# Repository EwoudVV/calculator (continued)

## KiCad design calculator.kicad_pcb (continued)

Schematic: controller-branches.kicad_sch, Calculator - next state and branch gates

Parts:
C1001, C1002, C1003, C1004, C1005, C1006, C1007, C1008, C1009, C1010, C1011, C1012, C1024, C1025, C1027, C1028, C1029, C1030, C1031, C1032, C1033, C1034: 100n; C_0603_1608Metric
U1001, U1004, U1023, U1028: SN74HC04PWR; TSSOP-14_4.4x5mm_P0.65mm
U1002, U1032: SN74HC08PWR; TSSOP-14_4.4x5mm_P0.65mm
U1003, U1007, U1008, U1009, U1010, U1012: SN74HC32PWR; TSSOP-14_4.4x5mm_P0.65mm
U1005, U1006, U1030: SN74HC00PWR; TSSOP-14_4.4x5mm_P0.65mm
U1011: CD74HC27M96; SOIC-14_3.9x8.7mm_P1.27mm
U1017: SN74HC10DR; SOIC-14_3.9x8.7mm_P1.27mm
U1024, U1025, U1033, U1034: CD74HC30M96; SOIC-14_3.9x8.7mm_P1.27mm
U1027, U1029, U1031: SN74HC20DR; SOIC-14_3.9x8.7mm_P1.27mm

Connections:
+5V: C1001.1, C1002.1, C1003.1, C1004.1, C1005.1, C1006.1, C1007.1, C1008.1, C1009.1, C1010.1, C1011.1, C1012.1, C1024.1, C1025.1, C1027.1, C1028.1, C1029.1, C1030.1, C1031.1, C1032.1, C1033.1, C1034.1, U1001.14 (VCC), U1002.14 (VCC), U1003.14 (VCC), U1004.14 (VCC), U1005.14 (VCC), U1006.14 (VCC), U1007.14 (VCC), U1008.14 (VCC), U1009.14 (VCC), U1010.14 (VCC), U1011.14 (VCC), U1012.14 (VCC), U1024.14 (VCC), U1025.12, U1025.14 (VCC), U1027.14 (VCC), U1028.14 (VCC), U1029.14 (VCC), U1030.14 (VCC), U1031.14 (VCC), U1032.2, U1032.14 (VCC), U1033.14 (VCC), U1034.12, U1034.14 (VCC); also elsewhere on the board
/Main controller/Branch decisions/ADVANCE_REQUEST: U1002.9, U1012.3
/Main controller/Branch decisions/ADVANCE_REQUEST_OR_36: U1010.6, U1010.12
/Main controller/Branch decisions/ADVANCE_REQUEST_OR_37: U1010.8, U1010.13
/Main controller/Branch decisions/ADVANCE_REQUEST_OR_38: U1010.11, U1012.1
/Main controller/Branch decisions/ANY_COMMAND: U1010.9, U1031.6
/Main controller/Branch decisions/CONTROLLER_POWER_RESET: U1001.10, U1003.9
/Main controller/Branch decisions/FORCE_CLEAR_OR_9: U1003.8, U1003.12
/Main controller/Branch decisions/INVALID_CODE_OR_7: U1003.3, U1003.4
/Main controller/Branch decisions/INVALID_LOW_CODE: U1003.1, U1029.8
/Main controller/Branch decisions/JUMP_SELECTED: U1002.12, U1030.6
/Main controller/Branch decisions/JUMP_SELECTED_GROUP_0: U1028.11, U1033.8
/Main controller/Branch decisions/JUMP_SELECTED_GROUP_1: U1028.13, U1034.8
/Main controller/Branch decisions/LOAD_BRANCH: U1002.11, U1012.5
/Main controller/Branch decisions/LOAD_REQUEST: U1004.9, U1012.6
/Main controller/Branch decisions/N_CANCEL: U1001.12, U1002.2
/Main controller/Branch decisions/N_CARRY_FLAG: U1001.2, U1007.10, U1008.5
/Main controller/Branch decisions/N_DIV_STAGE_LAST: U1001.8
/Main controller/Branch decisions/N_JUMP_SELECTED_GROUP_0: U1028.10, U1030.4
/Main controller/Branch decisions/N_JUMP_SELECTED_GROUP_1: U1028.12, U1030.5
/Main controller/Branch decisions/N_SHARED_PRODUCT_1_N_GROUP_0: U1006.12, U1023.4
/Main controller/Branch decisions/N_SHARED_PRODUCT_1_N_GROUP_1: U1006.13, U1023.6
/Main controller/Branch decisions/N_S_IDLE_N: U1002.4, U1004.4, U1011.13
/Main controller/Branch decisions/N_UPPER_FLAG: U1001.6, U1007.2, U1008.10
/Main controller/Branch decisions/N_ZERO_FLAG: U1001.4, U1007.13, U1008.2, U1008.13, U1009.5
/Main controller/Branch decisions/SHARED_PRODUCT_1_N_GROUP_0: U1023.3, U1024.8
/Main controller/Branch decisions/SHARED_PRODUCT_1_N_GROUP_1: U1023.5, U1025.8
/Main controller/Branch decisions/SINGLE_CLOCK_STATE: U1010.4, U1011.12
ACCEPT_ENTER_A_N: U1006.3, U1024.1, U1031.1; also elsewhere on the board
ACCEPT_ENTER_B_N: U1006.6, U1024.2, U1031.2; also elsewhere on the board
ACCEPT_NEW_ENTRY_N: U1006.8, U1017.9, U1031.4; also elsewhere on the board
ACCEPT_START_ADD_N: U1005.3, U1029.1, U1033.1; also elsewhere on the board
ACCEPT_START_DIV_N: U1004.5, U1005.11, U1017.10, U1029.2; also elsewhere on the board
ACCEPT_START_MUL_N: U1005.8, U1027.1, U1029.4; also elsewhere on the board
ACCEPT_START_SUB_N: U1005.6, U1029.5, U1033.2; also elsewhere on the board
ACTION_ALLOWED_CTRL: U1002.3, U1002.5; also elsewhere on the board
BRANCH_ADD_CHECK_0_N: U1007.6, U1024.3
BRANCH_ADD_CHECK_1_N: U1007.3, U1024.4; also elsewhere on the board
BRANCH_D_BORROW_0_N: U1009.8, U1033.3; also elsewhere on the board
BRANCH_D_B_ZERO_1_N: U1009.6, U1024.5; also elsewhere on the board
BRANCH_D_ROUND_0_N: U1010.3, U1024.6; also elsewhere on the board
BRANCH_D_STAGE_0_N: U1009.11, U1027.2; also elsewhere on the board
BRANCH_M_AGAIN_0_N: U1009.3, U1033.4; also elsewhere on the board
BRANCH_M_AGAIN_1_N: U1008.11, U1024.11
BRANCH_M_A_ZERO_1_N: U1007.11, U1027.4; also elsewhere on the board
BRANCH_M_B_ZERO_1_N: U1008.3, U1027.5; also elsewhere on the board
BRANCH_M_LIMIT_1_N: U1008.8, U1024.12; also elsewhere on the board
BRANCH_M_ORDER_1_N: U1008.6, U1033.5; also elsewhere on the board
BRANCH_SUB_CHECK_1_N: U1007.8, U1025.1
CALC_STARTED: U1032.3; also elsewhere on the board
CANCEL: U1001.13, U1003.10, U1010.10; also elsewhere on the board
CARRY_FLAG: U1001.1, U1009.10, U1010.2; also elsewhere on the board
DISPLAY_MODE: U1011.2; also elsewhere on the board
DIV_STAGE_LAST: U1001.9, U1009.13; also elsewhere on the board
DIV_STARTED: U1004.6; also elsewhere on the board
ENTER_A: U1006.2; also elsewhere on the board
ENTER_B: U1006.5; also elsewhere on the board
FORCE_CLEAR: U1003.11, U1004.1, U1012.4; also elsewhere on the board
GND: C1001.2, C1002.2, C1003.2, C1004.2, C1005.2, C1006.2, C1007.2, C1008.2, C1009.2, C1010.2, C1011.2, C1012.2, C1024.2, C1025.2, C1027.2, C1028.2, C1029.2, C1030.2, C1031.2, C1032.2, C1033.2, C1034.2, U1001.7 (GND), U1002.7 (GND), U1003.7 (GND), U1004.7 (GND), U1005.7 (GND), U1006.7 (GND), U1007.7 (GND), U1008.7 (GND), U1009.7 (GND), U1010.7 (GND), U1011.3, U1011.4, U1011.5, U1011.7 (GND), U1011.9, U1011.10, U1011.11, U1012.7 (GND), U1024.7 (GND), U1025.7 (GND), U1027.7 (GND), U1028.7 (GND), U1029.7 (GND), U1030.7 (GND), U1031.7 (GND), U1032.4, U1032.5, U1032.7 (GND), U1032.9, U1032.10, U1032.12, U1032.13, U1033.7 (GND), U1034.7 (GND); also elsewhere on the board
IDLE_READY: U1002.6, U1005.1, U1005.4, U1005.9, U1005.12, U1006.1, U1006.4, U1006.9; also elsewhere on the board
INVALID_CODE: U1003.6, U1003.13, U1012.2
MAIN_LOAD_N: U1004.8; also elsewhere on the board
NEW_ENTRY: U1006.10; also elsewhere on the board
NORMAL_BRANCH_ALLOWED: U1004.2; also elsewhere on the board
POWER_RESET_N: U1001.11, U1002.1, U1002.10; also elsewhere on the board
SEQUENCE_DONE: U1010.5; also elsewhere on the board
SHARED_PRODUCT_1: U1023.8, U1033.6; also elsewhere on the board
SHARED_PRODUCT_1_N: U1006.11, U1023.9
SHARED_PRODUCT_3: U1023.12, U1033.11; also elsewhere on the board
SHARED_PRODUCT_3_N: U1017.8, U1023.13
SHARED_PRODUCT_4: U1028.2, U1033.12; also elsewhere on the board
SHARED_PRODUCT_4_N: U1027.6, U1028.1
SHARED_PRODUCT_6: U1028.6, U1031.5
SHARED_PRODUCT_6_N: U1028.5, U1029.6, U1032.1
SHARED_PRODUCT_7: U1028.8, U1034.1; also elsewhere on the board
SHARED_PRODUCT_7_N: U1028.9, U1030.3
START_ADD: U1005.2; also elsewhere on the board
START_DIV: U1005.13; also elsewhere on the board
START_MUL: U1005.10; also elsewhere on the board
START_SUB: U1005.5; also elsewhere on the board
STATE_6: U1003.2; also elsewhere on the board
STATE_7: U1003.5; also elsewhere on the board
STATE_ADVANCE: U1002.8, U1002.13; also elsewhere on the board
STATE_GROUP_7_N: U1029.9; also elsewhere on the board
S_ADD_CHECK_N: U1007.1, U1007.4; also elsewhere on the board
S_CLEAR_DISPLAY_N: U1030.1; also elsewhere on the board
S_DIV_ZERO_N: U1034.2; also elsewhere on the board
S_DONE_A_N: U1034.3; also elsewhere on the board
S_DONE_W_N: U1030.2; also elsewhere on the board
S_D_BORROW_N: U1009.9; also elsewhere on the board
S_D_B_ZERO_N: U1009.4; also elsewhere on the board
S_D_INCREMENT_N: U1025.2; also elsewhere on the board
S_D_Q_INC_N: U1017.11; also elsewhere on the board
S_D_ROUND_N: U1010.1; also elsewhere on the board
S_D_STAGE_N: U1009.12; also elsewhere on the board
S_E_CLEAR_WAIT_N: U1025.3; also elsewhere on the board
S_E_DISPLAY_A_N: U1034.4; also elsewhere on the board
S_E_DISPLAY_B_N: U1034.5; also elsewhere on the board
S_E_NEW_WAIT_N: U1025.4; also elsewhere on the board
S_E_SHIFT_A_N: U1025.5; also elsewhere on the board
S_E_SHIFT_B_N: U1034.6; also elsewhere on the board
S_IDLE_N: U1004.3; also elsewhere on the board
S_INVALID_53_N: U1029.10; also elsewhere on the board
S_INVALID_54_N: U1029.12; also elsewhere on the board
S_INVALID_55_N: U1029.13; also elsewhere on the board
S_M_AGAIN_N: U1008.12, U1009.1; also elsewhere on the board
S_M_A_ZERO_N: U1007.12; also elsewhere on the board
S_M_B_ZERO_N: U1008.1; also elsewhere on the board
S_M_LIMIT_N: U1008.9; also elsewhere on the board
S_M_ORDER_N: U1008.4; also elsewhere on the board
S_OVERFLOW_N: U1034.11; also elsewhere on the board
S_SET_MINUS_N: U1025.6; also elsewhere on the board
S_SUB_CHECK_N: U1007.9; also elsewhere on the board
S_ZERO_W_N: U1025.11; also elsewhere on the board
UPPER_FLAG: U1001.5, U1007.5; also elsewhere on the board
WORD_MODE: U1011.1; also elsewhere on the board
ZERO_FLAG: U1001.3, U1009.2; also elsewhere on the board

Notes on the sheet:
Gate power and local decoupling

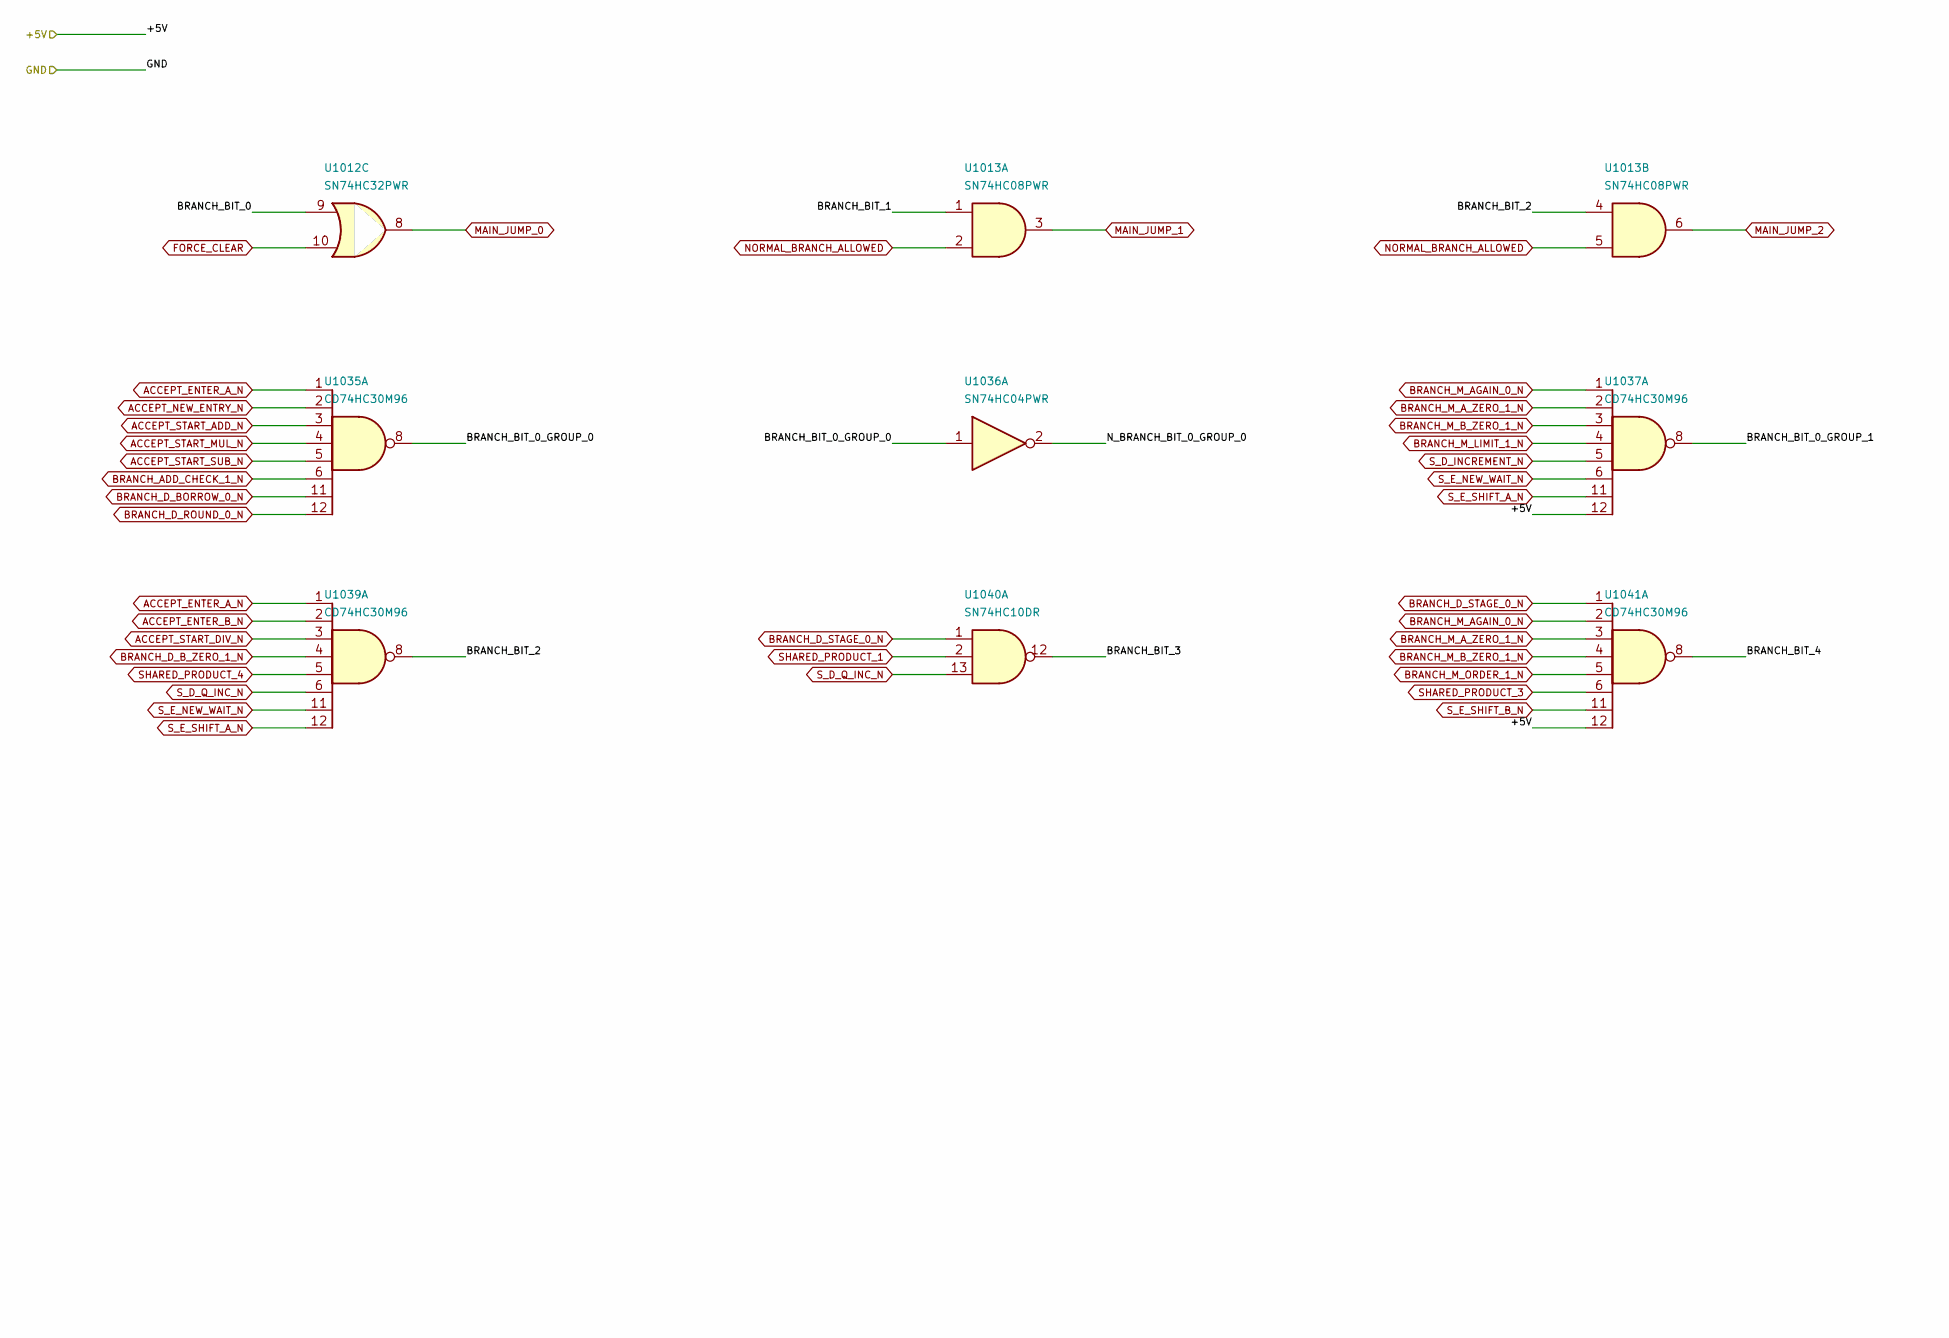
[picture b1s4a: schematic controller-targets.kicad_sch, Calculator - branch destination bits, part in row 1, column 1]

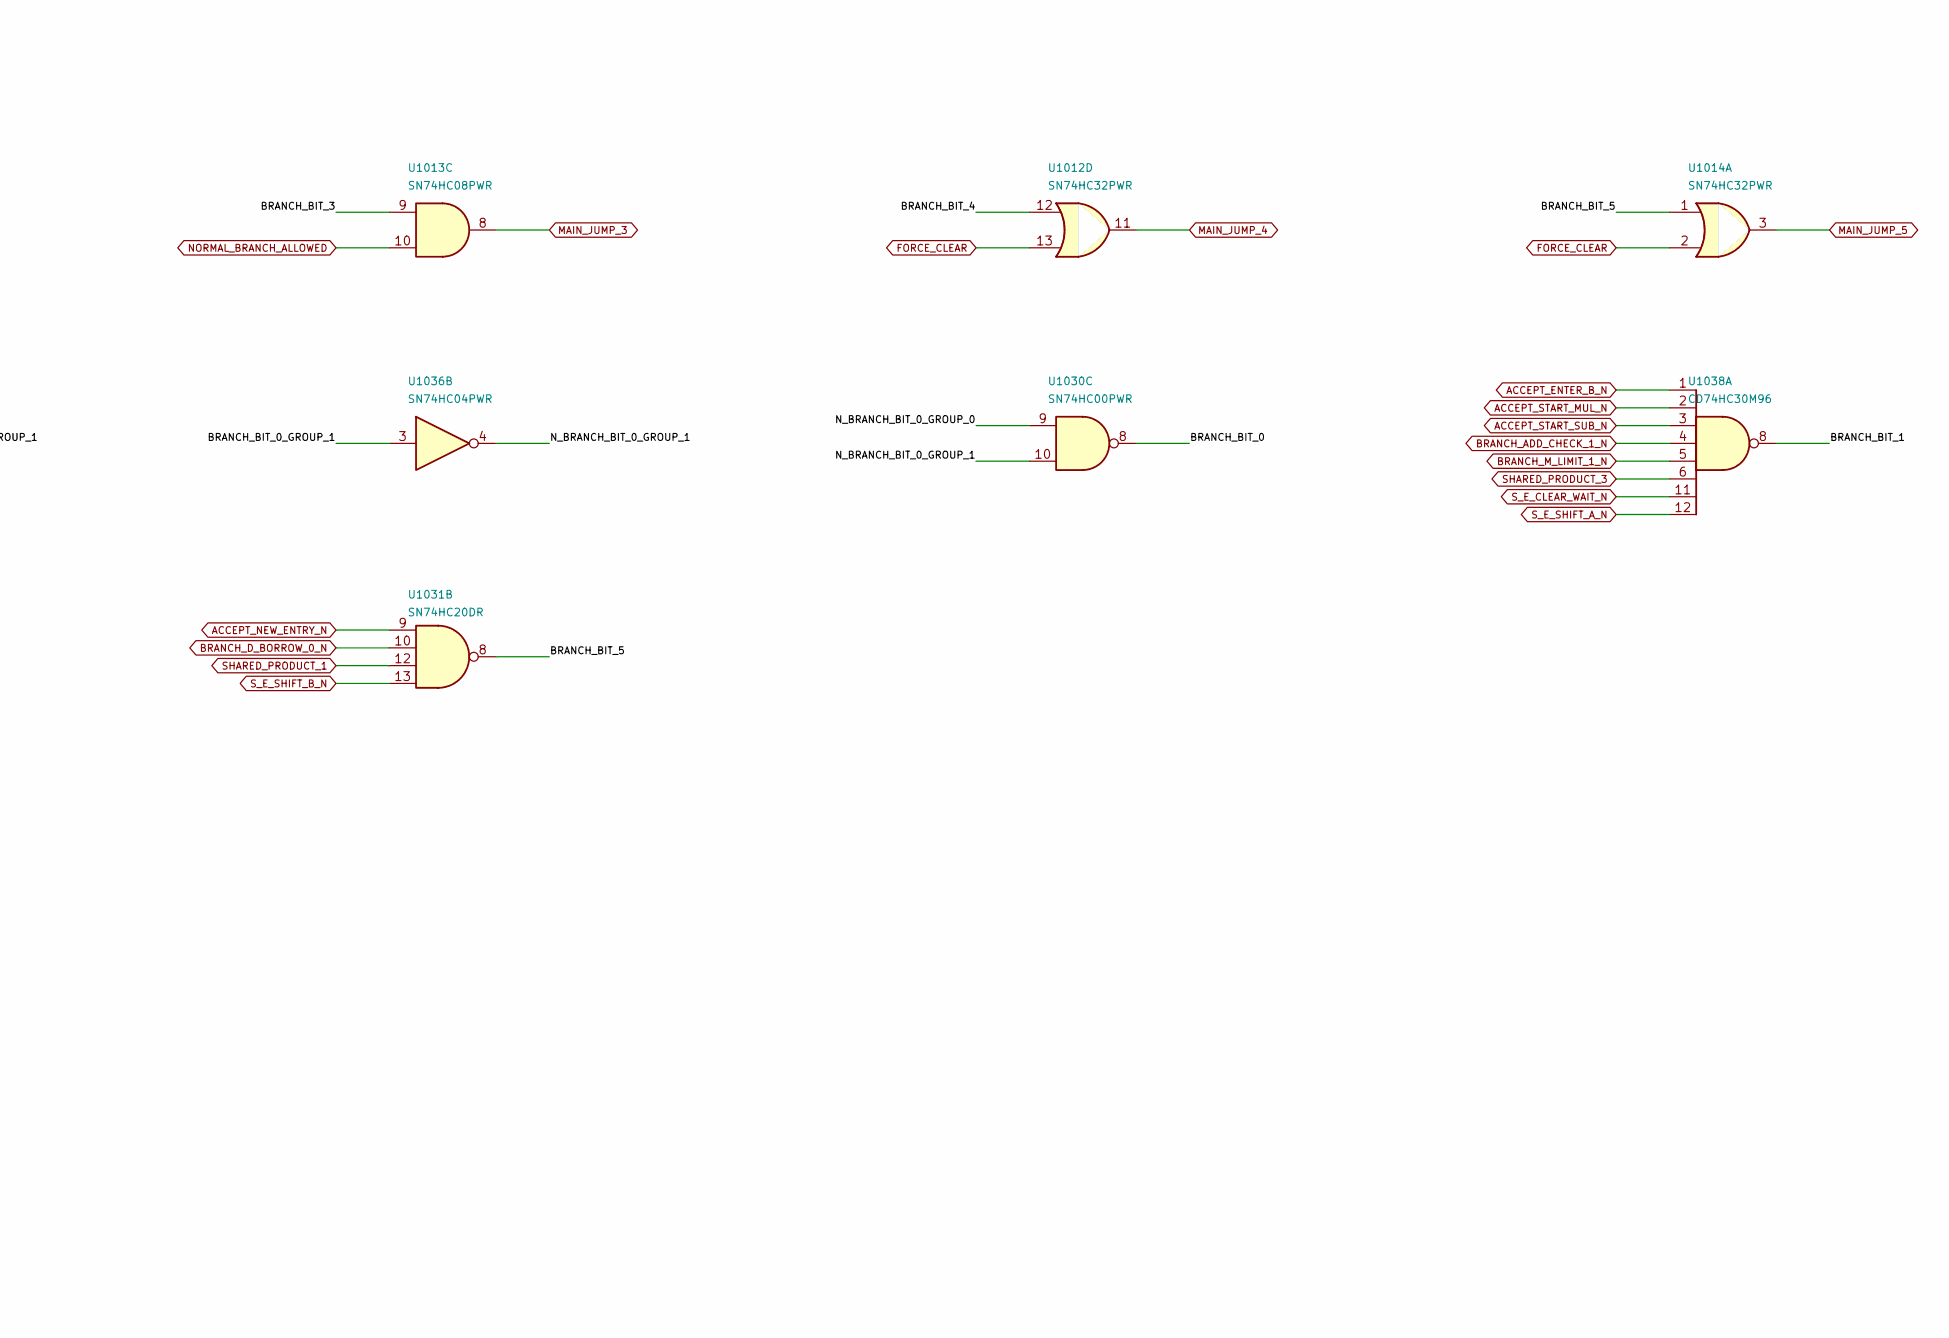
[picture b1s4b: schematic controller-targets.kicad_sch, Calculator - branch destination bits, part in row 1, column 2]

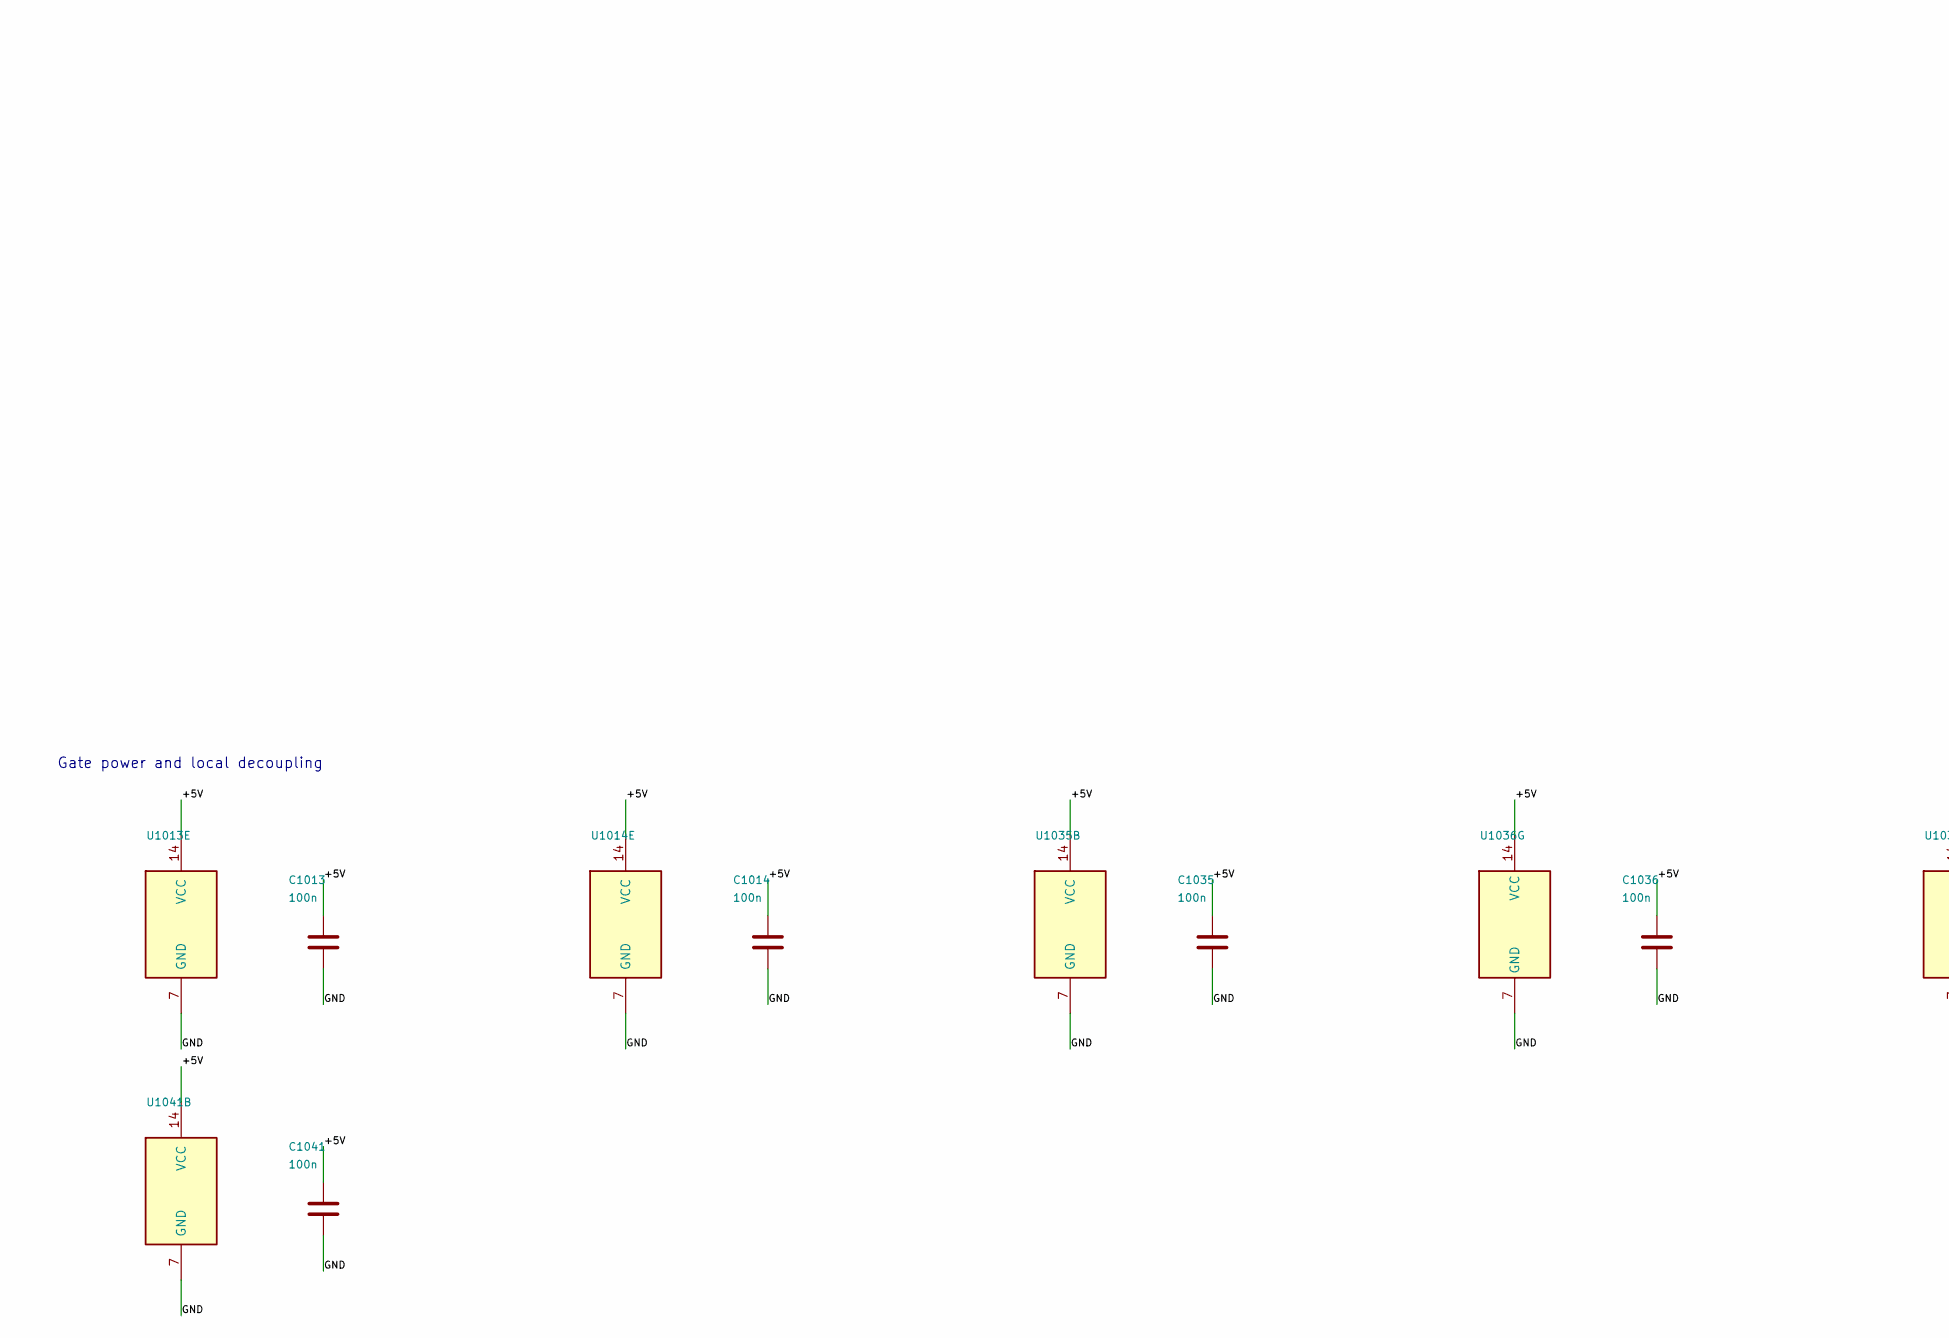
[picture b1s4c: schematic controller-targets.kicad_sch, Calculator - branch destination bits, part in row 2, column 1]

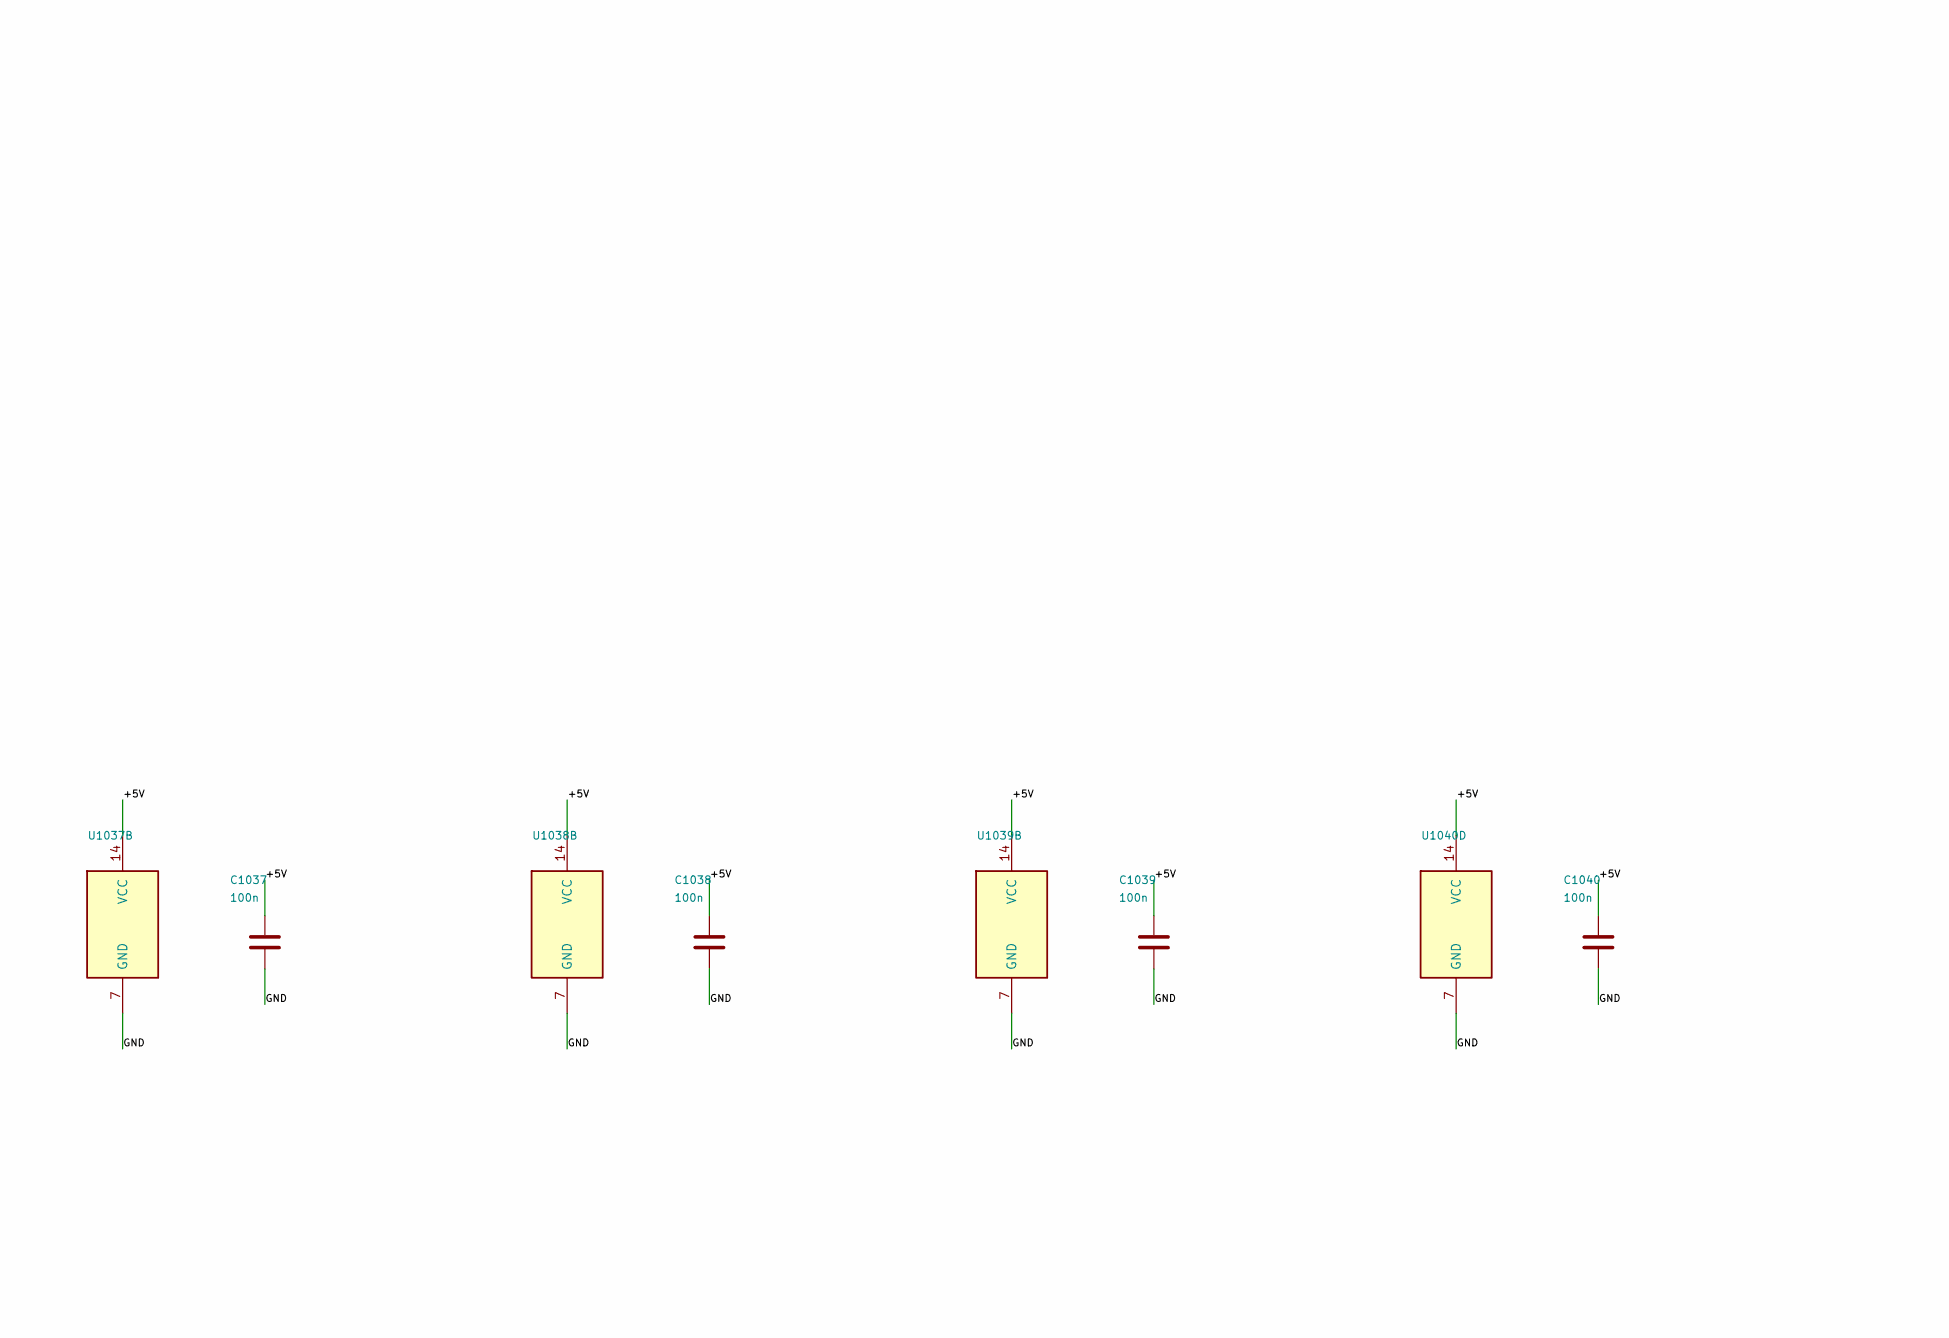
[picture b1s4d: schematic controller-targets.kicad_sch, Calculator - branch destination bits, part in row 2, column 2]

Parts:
C1013, C1014, C1035, C1036, C1037, C1038, C1039, C1040, C1041: 100n; C_0603_1608Metric
U1012, U1014: SN74HC32PWR; TSSOP-14_4.4x5mm_P0.65mm
U1013: SN74HC08PWR; TSSOP-14_4.4x5mm_P0.65mm
U1030: SN74HC00PWR; TSSOP-14_4.4x5mm_P0.65mm
U1031: SN74HC20DR; SOIC-14_3.9x8.7mm_P1.27mm
U1035, U1037, U1038, U1039, U1041: CD74HC30M96; SOIC-14_3.9x8.7mm_P1.27mm
U1036: SN74HC04PWR; TSSOP-14_4.4x5mm_P0.65mm
U1040: SN74HC10DR; SOIC-14_3.9x8.7mm_P1.27mm

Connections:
+5V: C1013.1, C1014.1, C1035.1, C1036.1, C1037.1, C1038.1, C1039.1, C1040.1, C1041.1, U1013.14 (VCC), U1014.14 (VCC), U1035.14 (VCC), U1036.14 (VCC), U1037.12, U1037.14 (VCC), U1038.14 (VCC), U1039.14 (VCC), U1040.14 (VCC), U1041.12, U1041.14 (VCC); also elsewhere on the board
/Main controller/Branch destinations/BRANCH_BIT_0: U1012.9, U1030.8
/Main controller/Branch destinations/BRANCH_BIT_0_GROUP_0: U1035.8, U1036.1
/Main controller/Branch destinations/BRANCH_BIT_0_GROUP_1: U1036.3, U1037.8
/Main controller/Branch destinations/BRANCH_BIT_1: U1013.1, U1038.8
/Main controller/Branch destinations/BRANCH_BIT_2: U1013.4, U1039.8
/Main controller/Branch destinations/BRANCH_BIT_3: U1013.9, U1040.12
/Main controller/Branch destinations/BRANCH_BIT_4: U1012.12, U1041.8
/Main controller/Branch destinations/BRANCH_BIT_5: U1014.1, U1031.8
/Main controller/Branch destinations/N_BRANCH_BIT_0_GROUP_0: U1030.9, U1036.2
/Main controller/Branch destinations/N_BRANCH_BIT_0_GROUP_1: U1030.10, U1036.4
ACCEPT_ENTER_A_N: U1035.1, U1039.1; also elsewhere on the board
ACCEPT_ENTER_B_N: U1038.1, U1039.2; also elsewhere on the board
ACCEPT_NEW_ENTRY_N: U1031.9, U1035.2; also elsewhere on the board
ACCEPT_START_ADD_N: U1035.3; also elsewhere on the board
ACCEPT_START_DIV_N: U1039.3; also elsewhere on the board
ACCEPT_START_MUL_N: U1035.4, U1038.2; also elsewhere on the board
ACCEPT_START_SUB_N: U1035.5, U1038.3; also elsewhere on the board
BRANCH_ADD_CHECK_1_N: U1035.6, U1038.4; also elsewhere on the board
BRANCH_D_BORROW_0_N: U1031.10, U1035.11; also elsewhere on the board
BRANCH_D_B_ZERO_1_N: U1039.4; also elsewhere on the board
BRANCH_D_ROUND_0_N: U1035.12; also elsewhere on the board
BRANCH_D_STAGE_0_N: U1040.1, U1041.1; also elsewhere on the board
BRANCH_M_AGAIN_0_N: U1037.1, U1041.2; also elsewhere on the board
BRANCH_M_A_ZERO_1_N: U1037.2, U1041.3; also elsewhere on the board
BRANCH_M_B_ZERO_1_N: U1037.3, U1041.4; also elsewhere on the board
BRANCH_M_LIMIT_1_N: U1037.4, U1038.5; also elsewhere on the board
BRANCH_M_ORDER_1_N: U1041.5; also elsewhere on the board
FORCE_CLEAR: U1012.10, U1012.13, U1014.2; also elsewhere on the board
GND: C1013.2, C1014.2, C1035.2, C1036.2, C1037.2, C1038.2, C1039.2, C1040.2, C1041.2, U1013.7 (GND), U1014.7 (GND), U1035.7 (GND), U1036.7 (GND), U1037.7 (GND), U1038.7 (GND), U1039.7 (GND), U1040.7 (GND), U1041.7 (GND); also elsewhere on the board
MAIN_JUMP_0: U1012.8; also elsewhere on the board
MAIN_JUMP_1: U1013.3; also elsewhere on the board
MAIN_JUMP_2: U1013.6; also elsewhere on the board
MAIN_JUMP_3: U1013.8; also elsewhere on the board
MAIN_JUMP_4: U1012.11; also elsewhere on the board
MAIN_JUMP_5: U1014.3; also elsewhere on the board
NORMAL_BRANCH_ALLOWED: U1013.2, U1013.5, U1013.10; also elsewhere on the board
SHARED_PRODUCT_1: U1031.12, U1040.2; also elsewhere on the board
SHARED_PRODUCT_3: U1038.6, U1041.6; also elsewhere on the board
SHARED_PRODUCT_4: U1039.5; also elsewhere on the board
S_D_INCREMENT_N: U1037.5; also elsewhere on the board
S_D_Q_INC_N: U1039.6, U1040.13; also elsewhere on the board
S_E_CLEAR_WAIT_N: U1038.11; also elsewhere on the board
S_E_NEW_WAIT_N: U1037.6, U1039.11; also elsewhere on the board
S_E_SHIFT_A_N: U1037.11, U1038.12, U1039.12; also elsewhere on the board
S_E_SHIFT_B_N: U1031.13, U1041.11; also elsewhere on the board

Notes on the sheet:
Gate power and local decoupling

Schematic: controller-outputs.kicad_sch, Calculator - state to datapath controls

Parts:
C1015, C1016, C1017, C1018, C1026, C1042, C1043, C1044, C1045, C1046, C1047, C1048, C1049, C1050, C1051: 100n; C_0603_1608Metric
U1004, U1016, U1023, U1028, U1036, U1048, U1051: SN74HC04PWR; TSSOP-14_4.4x5mm_P0.65mm
U1013, U1015, U1018: SN74HC08PWR; TSSOP-14_4.4x5mm_P0.65mm
U1014: SN74HC32PWR; TSSOP-14_4.4x5mm_P0.65mm
U1017, U1040, U1049: SN74HC10DR; SOIC-14_3.9x8.7mm_P1.27mm
U1026, U1042, U1043, U1047: CD74HC30M96; SOIC-14_3.9x8.7mm_P1.27mm
U1027, U1044, U1046: SN74HC20DR; SOIC-14_3.9x8.7mm_P1.27mm
U1030, U1045, U1050: SN74HC00PWR; TSSOP-14_4.4x5mm_P0.65mm

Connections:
+5V: C1015.1, C1016.1, C1017.1, C1018.1, C1026.1, C1042.1, C1043.1, C1044.1, C1045.1, C1046.1, C1047.1, C1048.1, C1049.1, C1050.1, C1051.1, U1015.14 (VCC), U1016.14 (VCC), U1017.14 (VCC), U1018.14 (VCC), U1026.14 (VCC), U1042.14 (VCC), U1043.6, U1043.11, U1043.12, U1043.14 (VCC), U1044.14 (VCC), U1045.14 (VCC), U1046.14 (VCC), U1047.14 (VCC), U1048.14 (VCC), U1049.14 (VCC), U1050.14 (VCC), U1051.14 (VCC); also elsewhere on the board
/Main controller/Datapath controls/N_DIV_STAGE_LAST: U1016.2, U1017.2
/Main controller/Datapath controls/N_STAGE_INC: U1016.3, U1017.12
/Main controller/Datapath controls/N_WORD_MODE_GROUP_0: U1030.12, U1036.6
/Main controller/Datapath controls/N_WORD_MODE_GROUP_1: U1030.13, U1036.8
/Main controller/Datapath controls/OPPOSITE_MAC_Y_0: U1004.11, U1040.8
/Main controller/Datapath controls/OPPOSITE_MAC_Y_1: U1004.13, U1046.8
/Main controller/Datapath controls/RAW_MAC_BANK_RESET: U1015.1, U1050.3
/Main controller/Datapath controls/RAW_Q_INC: U1015.9, U1048.10
/Main controller/Datapath controls/RAW_Q_RESET: U1015.4, U1048.8
/Main controller/Datapath controls/RAW_SIGN_SET: U1013.12, U1048.6
/Main controller/Datapath controls/RAW_STAGE_INC: U1017.1, U1051.2
/Main controller/Datapath controls/RAW_STAGE_RESET: U1015.12, U1048.12
/Main controller/Datapath controls/RESULT_DISPLAY: U1018.4, U1050.6
/Main controller/Datapath controls/RESULT_DISPLAY_FINISHED: U1014.4, U1018.6
/Main controller/Datapath controls/RESULT_ERROR: U1014.5, U1050.8
/Main controller/Datapath controls/WORD_MODE_GROUP_0: U1036.5, U1042.8
/Main controller/Datapath controls/WORD_MODE_GROUP_1: U1036.9, U1043.8
ACTION_ALLOWED_CTRL: U1013.13, U1015.2, U1015.5, U1015.10, U1015.13, U1017.13; also elsewhere on the board
CONST_ONE: U1045.8; also elsewhere on the board
DISPLAY_FINISHED: U1018.3; also elsewhere on the board
DISPLAY_MODE: U1018.1, U1044.6; also elsewhere on the board
DISPLAY_SOURCE_0: U1048.2; also elsewhere on the board
DISPLAY_SOURCE_1: U1048.4; also elsewhere on the board
DIV_STAGE_LAST: U1016.1; also elsewhere on the board
GND: C1015.2, C1016.2, C1017.2, C1018.2, C1026.2, C1042.2, C1043.2, C1044.2, C1045.2, C1046.2, C1047.2, C1048.2, C1049.2, C1050.2, C1051.2, U1015.7 (GND), U1016.7 (GND), U1017.7 (GND), U1018.7 (GND), U1026.7 (GND), U1042.7 (GND), U1043.7 (GND), U1044.7 (GND), U1045.7 (GND), U1046.7 (GND), U1047.7 (GND), U1048.7 (GND), U1049.7 (GND), U1049.9, U1049.10, U1049.11, U1050.7 (GND), U1050.12, U1050.13, U1051.3, U1051.5, U1051.7 (GND), U1051.9, U1051.11, U1051.13; also elsewhere on the board
LEFT_SELECT_0: U1049.6; also elsewhere on the board
LEFT_SELECT_1: U1045.11; also elsewhere on the board
MAC_BANK_RESET: U1015.3; also elsewhere on the board
MAC_SHIFT_A: U1044.8; also elsewhere on the board
MAC_SHIFT_B: U1036.10; also elsewhere on the board
MAC_SHIFT_W: U1036.12; also elsewhere on the board
MAC_WRITE_A: U1045.3; also elsewhere on the board
MAC_WRITE_B: U1045.6; also elsewhere on the board
MAC_WRITE_W: U1046.6; also elsewhere on the board
MAC_X_0: U1047.8; also elsewhere on the board
MAC_X_1: U1040.6; also elsewhere on the board
MAC_Y_0: U1004.10; also elsewhere on the board
MAC_Y_1: U1004.12; also elsewhere on the board
Q_INC: U1015.8; also elsewhere on the board
Q_RESET: U1015.6; also elsewhere on the board
RESULT_FINISHED: U1014.6; also elsewhere on the board
SEQUENCE_DONE: U1018.2, U1018.5; also elsewhere on the board
SHARED_PRODUCT_2: U1023.10, U1040.3, U1042.1, U1046.1
SHARED_PRODUCT_2_N: U1023.11, U1026.8
SHARED_PRODUCT_5: U1028.4, U1046.9, U1049.1
SHARED_PRODUCT_5_N: U1027.8, U1028.3
SHARED_PRODUCT_7: U1044.1, U1048.3; also elsewhere on the board
SIGN_SET: U1013.11; also elsewhere on the board
STAGE_INC: U1016.4; also elsewhere on the board
STAGE_RESET: U1015.11; also elsewhere on the board
SUBTRACT: U1049.12; also elsewhere on the board
S_ADD_N: U1042.2, U1046.2, U1046.10; also elsewhere on the board
S_DIV_ZERO_N: U1050.9; also elsewhere on the board
S_DONE_A_N: U1044.2, U1050.4; also elsewhere on the board
S_DONE_W_N: U1050.5; also elsewhere on the board
S_D_APPEND_N: U1036.13, U1045.12, U1049.3; also elsewhere on the board
S_D_CLEAR_N: U1026.1, U1047.1; also elsewhere on the board
S_D_DOUBLE_N: U1026.2, U1040.9; also elsewhere on the board
S_D_INCREMENT_N: U1042.3, U1045.1, U1045.9; also elsewhere on the board
S_D_Q_INC_N: U1048.11; also elsewhere on the board
S_D_Q_RESET_N: U1048.9; also elsewhere on the board
S_D_RESTORE_N: U1026.3, U1046.12; also elsewhere on the board
S_D_ROUND_COMPARE_N: U1027.9, U1040.4, U1042.4; also elsewhere on the board
S_D_SCALE_1_N: U1044.9; also elsewhere on the board
S_D_SCALE_2_N: U1044.10; also elsewhere on the board
S_D_STAGE_N: U1051.1; also elsewhere on the board
S_D_START_N: U1048.13; also elsewhere on the board
S_D_STORE_Q_N: U1044.12, U1045.13; also elsewhere on the board
S_D_SUB_N: U1026.4, U1027.10; also elsewhere on the board
S_D_TEST_B_N: U1042.5, U1047.2; also elsewhere on the board
S_E_CLEAR_ASSERT_N: U1050.1; also elsewhere on the board
S_E_DISPLAY_A_N: U1044.4; also elsewhere on the board
S_E_DISPLAY_B_N: U1044.5, U1048.1; also elsewhere on the board
S_E_NEW_CLEAR_N: U1050.2; also elsewhere on the board
S_E_SHIFT_A_N: U1044.13, U1049.4; also elsewhere on the board
S_E_SHIFT_B_N: U1036.11, U1049.5; also elsewhere on the board
S_M_ADD_N: U1026.5, U1040.10, U1046.13; also elsewhere on the board
S_M_CLEAR_N: U1026.6, U1047.3; also elsewhere on the board
S_M_COMPARE_N: U1027.12, U1042.6; also elsewhere on the board
S_M_DEC_N: U1042.11, U1045.4, U1045.10, U1047.4, U1049.2; also elsewhere on the board
S_M_SAVE_N: U1042.12, U1046.4; also elsewhere on the board
S_M_SWAP_A_N: U1043.1, U1045.2, U1047.5; also elsewhere on the board
S_M_SWAP_B_N: U1040.5, U1043.2, U1045.5; also elsewhere on the board
S_M_TEST_A_N: U1043.3; also elsewhere on the board
S_M_TEST_B_N: U1043.4, U1047.6; also elsewhere on the board
S_NEGATE_N: U1026.11, U1040.11, U1047.11, U1049.13; also elsewhere on the board
S_OVERFLOW_N: U1050.10; also elsewhere on the board
S_SET_MINUS_N: U1048.5; also elsewhere on the board
S_SUB_N: U1027.13, U1043.5, U1046.5; also elsewhere on the board
S_ZERO_W_N: U1026.12, U1047.12; also elsewhere on the board
WORD_MODE: U1030.11; also elsewhere on the board

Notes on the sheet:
Gate power and local decoupling
